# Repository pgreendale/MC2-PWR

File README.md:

# MC2-PWR compact Eurorack Power Supply
85TE Modular Case - Powersupply

# Introduction 
This Project is a quick - and Dirty Powersupply, which I designed for my modular Eurorack Case. It is relatvely cheap to bild (<60€ for parts). 
To keep tings simple, it has a singlelayer design, which can be easily etched at home (i prefer photolithographic etching, big planes could be difficult to be done with toner transfer). 

# Features 
* +- 12V dual Power supply based on Linear regulators 
* common Gate/CV rail can be divided to use two groups with common Gate/CV
* two 1.5A Fuses to protect against overcurrent 
* screwhole with GND connection for shielding backplates if necessary 

# Parts 
* parts are ordered from Reichelt, a BOM is included in files. 

# Disclaimer 
This project was designed for experienced build. Especially the installation the transformer requires educated building of line powered electronics. To keep things safe, I recommend extra fusing the transformer against overheating and overcurrent on the primary side. Building and operating is done on your own risk! 

Please check the supply under load (take i.E. 10W 12V Lightbulbs from cars etc. one from gnd to +12V and one from gnd to -12V)  first before connecting any Eurorack modules to it. 

# Else 
License GPL v.3
If you like the design or feel the need to make it better, feel free to contact me.

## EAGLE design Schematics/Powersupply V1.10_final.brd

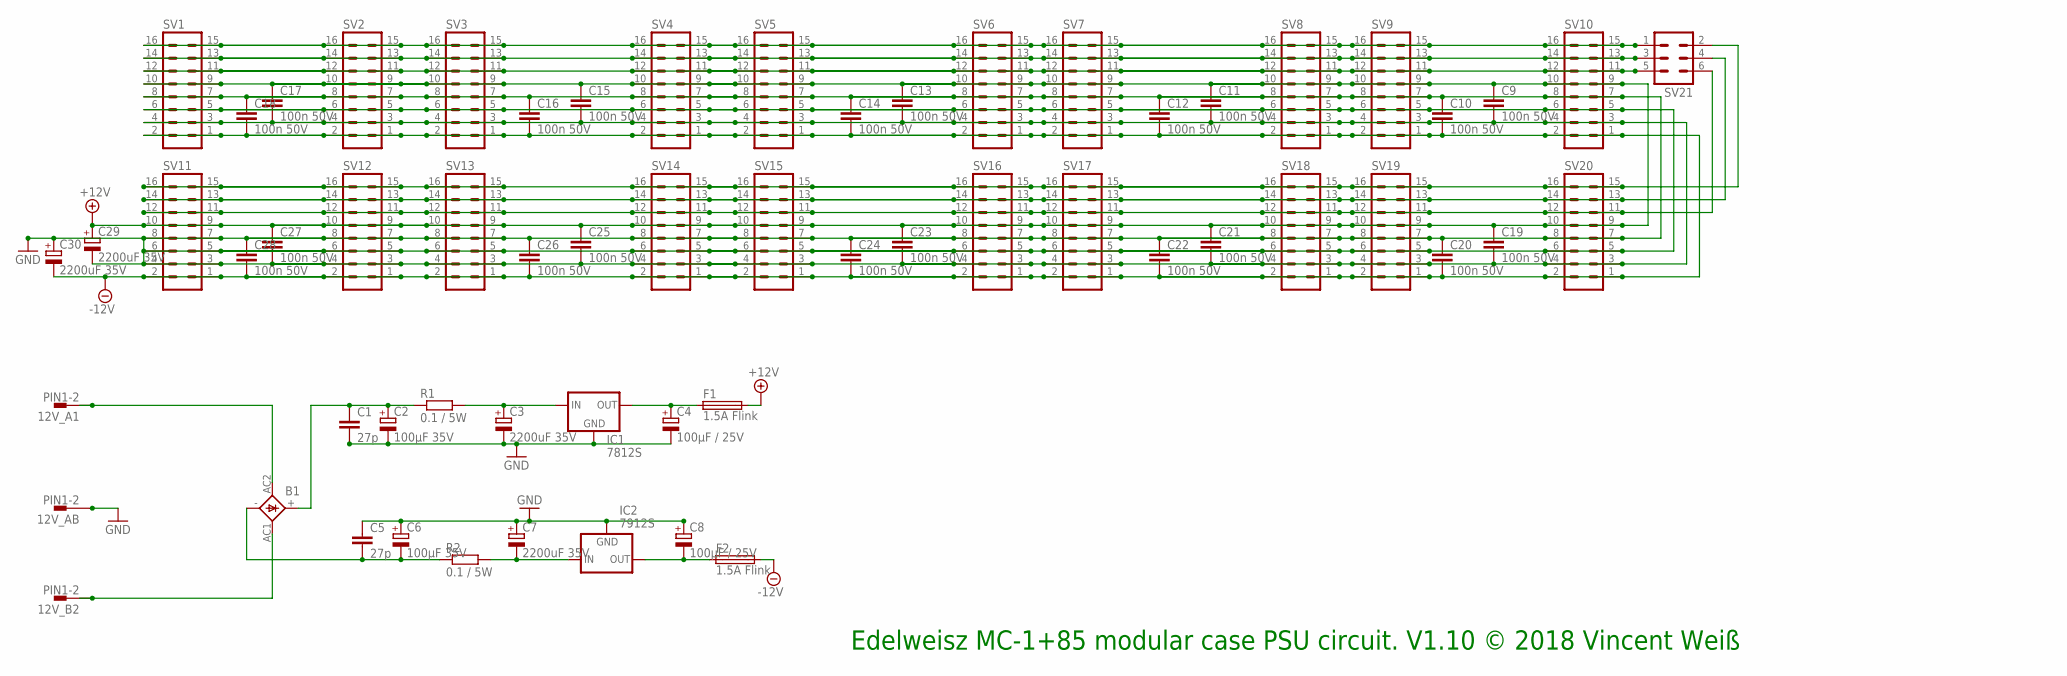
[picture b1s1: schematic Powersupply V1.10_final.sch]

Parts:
12V_A1, 12V_AB, 12V_B2: PIN1-2; 62221
B1: GBU4; GBU4S
C1, C5: 27p; C050-024X044
C2, C6: 100µF 35V; E2,5-7
C3, C7, C29, C30: 2200uF 35V; E7,5-16
C4, C8: 100µF / 25V; E2,5-7
C9, C10, C11, C12, C13, C14, C15, C16, C17, C18, C19, C20, C21, C22, C23, C24, C25, C26, C27, C28: 100n 50V; C025-025X050
F1, F2: 1.5A Flink; SH22,5
IC1: 7812S; 78XXS
IC2: 7912S; 79XXS
R1, R2: 0.1 / 5W; P0613/15
SV1, SV2, SV3, SV4, SV5, SV6, SV7, SV8, SV9, SV10, SV11, SV12, SV13, SV14, SV15, SV16, SV17, SV18, SV19, SV20: ML16
SV21: MA03-2

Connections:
+12V: C9.1, C11.1, C13.1, C15.1, C17.1, C19.1, C21.1, C23.1, C25.1, C27.1, C29.+, F1.2, SV1.9, SV1.10, SV2.9, SV2.10, SV3.9, SV3.10, SV4.9, SV4.10, SV5.9, SV5.10, SV6.9, SV6.10, SV7.9, SV7.10, SV8.9, SV8.10, SV9.9, SV9.10, SV10.9, SV10.10, SV11.9, SV11.10, SV12.9, SV12.10, SV13.9, SV13.10, SV14.9, SV14.10, SV15.9, SV15.10, SV16.9, SV16.10, SV17.9, SV17.10, SV18.9, SV18.10, SV19.9, SV19.10, SV20.9, SV20.10
-12V: C10.2, C12.2, C14.2, C16.2, C18.2, C20.2, C22.2, C24.2, C26.2, C28.2, C30.-, F2.2, SV1.1, SV1.2, SV2.1, SV2.2, SV3.1, SV3.2, SV4.1, SV4.2, SV5.1, SV5.2, SV6.1, SV6.2, SV7.1, SV7.2, SV8.1, SV8.2, SV9.1, SV9.2, SV10.1, SV10.2, SV11.1, SV11.2, SV12.1, SV12.2, SV13.1, SV13.2, SV14.1, SV14.2, SV15.1, SV15.2, SV16.1, SV16.2, SV17.1, SV17.2, SV18.1, SV18.2, SV19.1, SV19.2, SV20.1, SV20.2
GND: 12V_AB.1, C1.2, C2.-, C3.-, C4.-, C5.1, C6.+, C7.+, C8.+, C9.2, C10.1, C11.2, C12.1, C13.2, C14.1, C15.2, C16.1, C17.2, C18.1, C19.2, C20.1, C21.2, C22.1, C23.2, C24.1, C25.2, C26.1, C27.2, C28.1, C29.-, C30.+, IC1.GND, IC2.GND, SV1.3, SV1.4, SV1.5, SV1.6, SV1.7, SV1.8, SV2.3, SV2.4, SV2.5, SV2.6, SV2.7, SV2.8, SV3.3, SV3.4, SV3.5, SV3.6, SV3.7, SV3.8, SV4.3, SV4.4, SV4.5, SV4.6, SV4.7, SV4.8, SV5.3, SV5.4, SV5.5, SV5.6, SV5.7, SV5.8, SV6.3, SV6.4, SV6.5, SV6.6, SV6.7, SV6.8, SV7.3, SV7.4, SV7.5, SV7.6, SV7.7, SV7.8, SV8.3, SV8.4, SV8.5, SV8.6, SV8.7, SV8.8, SV9.3, SV9.4, SV9.5, SV9.6, SV9.7, SV9.8, SV10.3, SV10.4, SV10.5, SV10.6, SV10.7, SV10.8, SV11.3, SV11.4, SV11.5, SV11.6, SV11.7, SV11.8, SV12.3, SV12.4, SV12.5, SV12.6, SV12.7, SV12.8, SV13.3, SV13.4, SV13.5, SV13.6, SV13.7, SV13.8, SV14.3, SV14.4, SV14.5, SV14.6, SV14.7, SV14.8, SV15.3, SV15.4, SV15.5, SV15.6, SV15.7, SV15.8, SV16.3, SV16.4, SV16.5, SV16.6, SV16.7, SV16.8, SV17.3, SV17.4, SV17.5, SV17.6, SV17.7, SV17.8, SV18.3, SV18.4, SV18.5, SV18.6, SV18.7, SV18.8, SV19.3, SV19.4, SV19.5, SV19.6, SV19.7, SV19.8, SV20.3, SV20.4, SV20.5, SV20.6, SV20.7, SV20.8
unnamed: B1.-, C5.2, C6.-, R2.1
unnamed: 12V_A1.1, B1.AC2 (AC1)
unnamed: 12V_B2.1, B1.AC1 (AC2)
unnamed: B1.+, C1.1, C2.+, R1.1
unnamed: C3.+, IC1.IN, R1.2
unnamed: C7.-, IC2.IN, R2.2
unnamed: C4.+, F1.1, IC1.OUT
unnamed: C8.-, F2.1, IC2.OUT
unnamed: SV1.15, SV1.16, SV2.15, SV2.16, SV3.15, SV3.16, SV4.15, SV4.16, SV5.15, SV5.16, SV6.15, SV6.16, SV7.15, SV7.16, SV8.15, SV8.16, SV9.15, SV9.16, SV10.15, SV10.16, SV21.1
unnamed: SV1.13, SV1.14, SV2.13, SV2.14, SV3.13, SV3.14, SV4.13, SV4.14, SV5.13, SV5.14, SV6.13, SV6.14, SV7.13, SV7.14, SV8.13, SV8.14, SV9.13, SV9.14, SV10.13, SV10.14, SV21.3
unnamed: SV1.11, SV1.12, SV2.11, SV2.12, SV3.11, SV3.12, SV4.11, SV4.12, SV5.11, SV5.12, SV6.11, SV6.12, SV7.11, SV7.12, SV8.11, SV8.12, SV9.11, SV9.12, SV10.11, SV10.12, SV21.5
unnamed: SV11.11, SV11.12, SV12.11, SV12.12, SV13.11, SV13.12, SV14.11, SV14.12, SV15.11, SV15.12, SV16.11, SV16.12, SV17.11, SV17.12, SV18.11, SV18.12, SV19.11, SV19.12, SV20.11, SV20.12, SV21.6
unnamed: SV11.13, SV11.14, SV12.13, SV12.14, SV13.13, SV13.14, SV14.13, SV14.14, SV15.13, SV15.14, SV16.13, SV16.14, SV17.13, SV17.14, SV18.13, SV18.14, SV19.13, SV19.14, SV20.13, SV20.14, SV21.4
unnamed: SV11.15, SV11.16, SV12.15, SV12.16, SV13.15, SV13.16, SV14.15, SV14.16, SV15.15, SV15.16, SV16.15, SV16.16, SV17.15, SV17.16, SV18.15, SV18.16, SV19.15, SV19.16, SV20.15, SV20.16, SV21.2

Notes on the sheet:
Edelweisz MC-1+85 modular case PSU circuit. V1.10 © 2018 Vincent Weiß

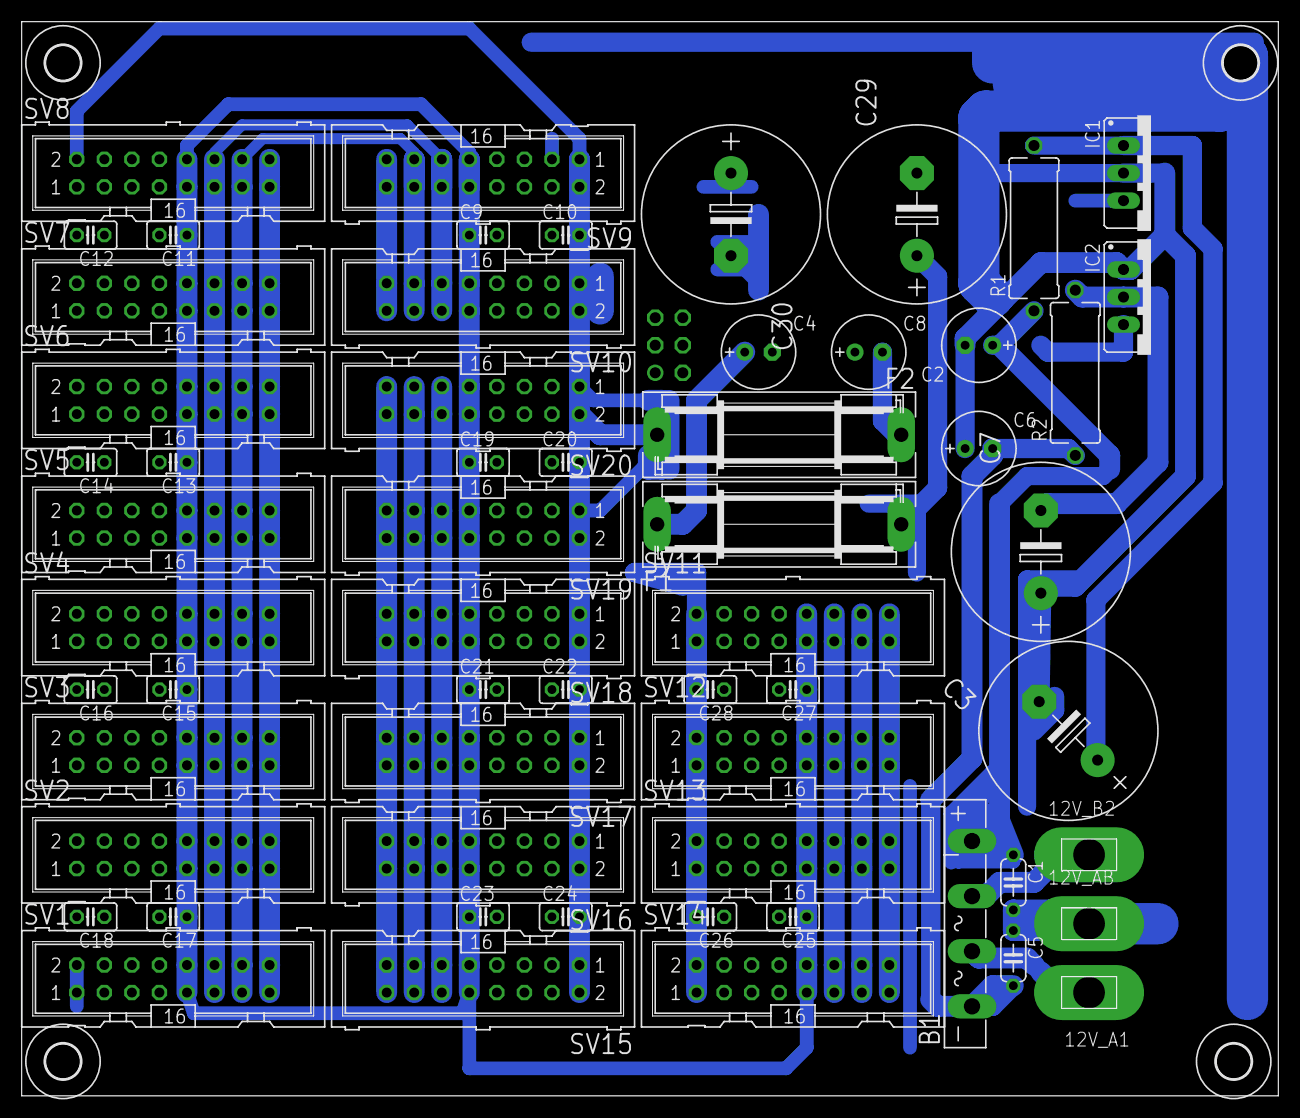
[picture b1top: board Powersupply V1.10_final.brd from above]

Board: 2 copper layers, 115.9 x 99.0 mm, 65 parts (1 on the bottom side), 17 nets.

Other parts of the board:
U$1, U$2, U$3, U$4: 3,2

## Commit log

2020-05-26 Add files via upload
    Added BOM, Schematics V1.10
2020-12-12 Update README.md
    minor corr
